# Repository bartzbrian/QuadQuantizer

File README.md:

# QuadQuantizer
quad pitch quant eurorack

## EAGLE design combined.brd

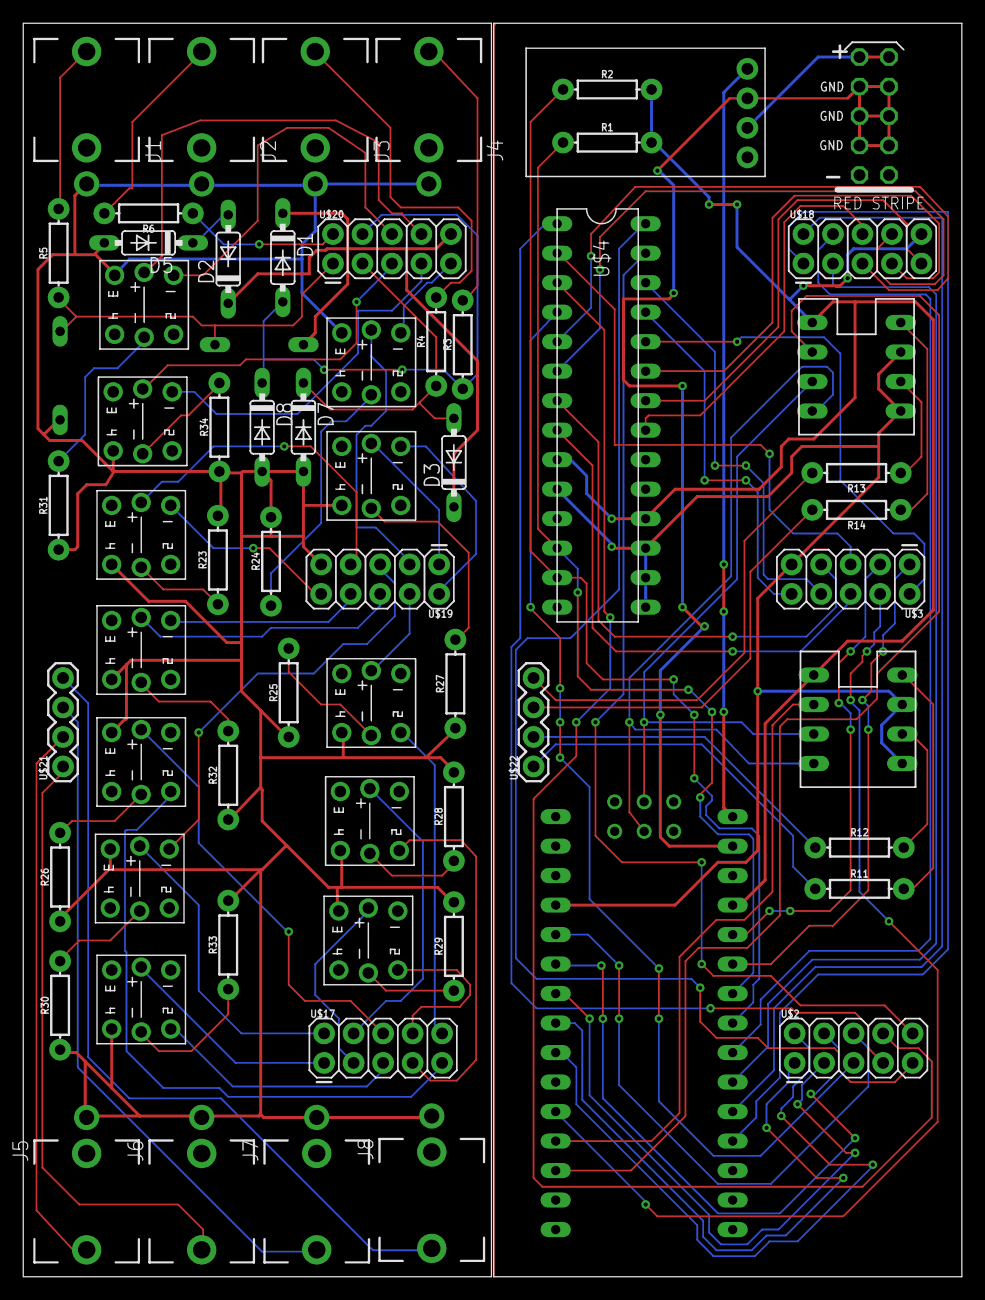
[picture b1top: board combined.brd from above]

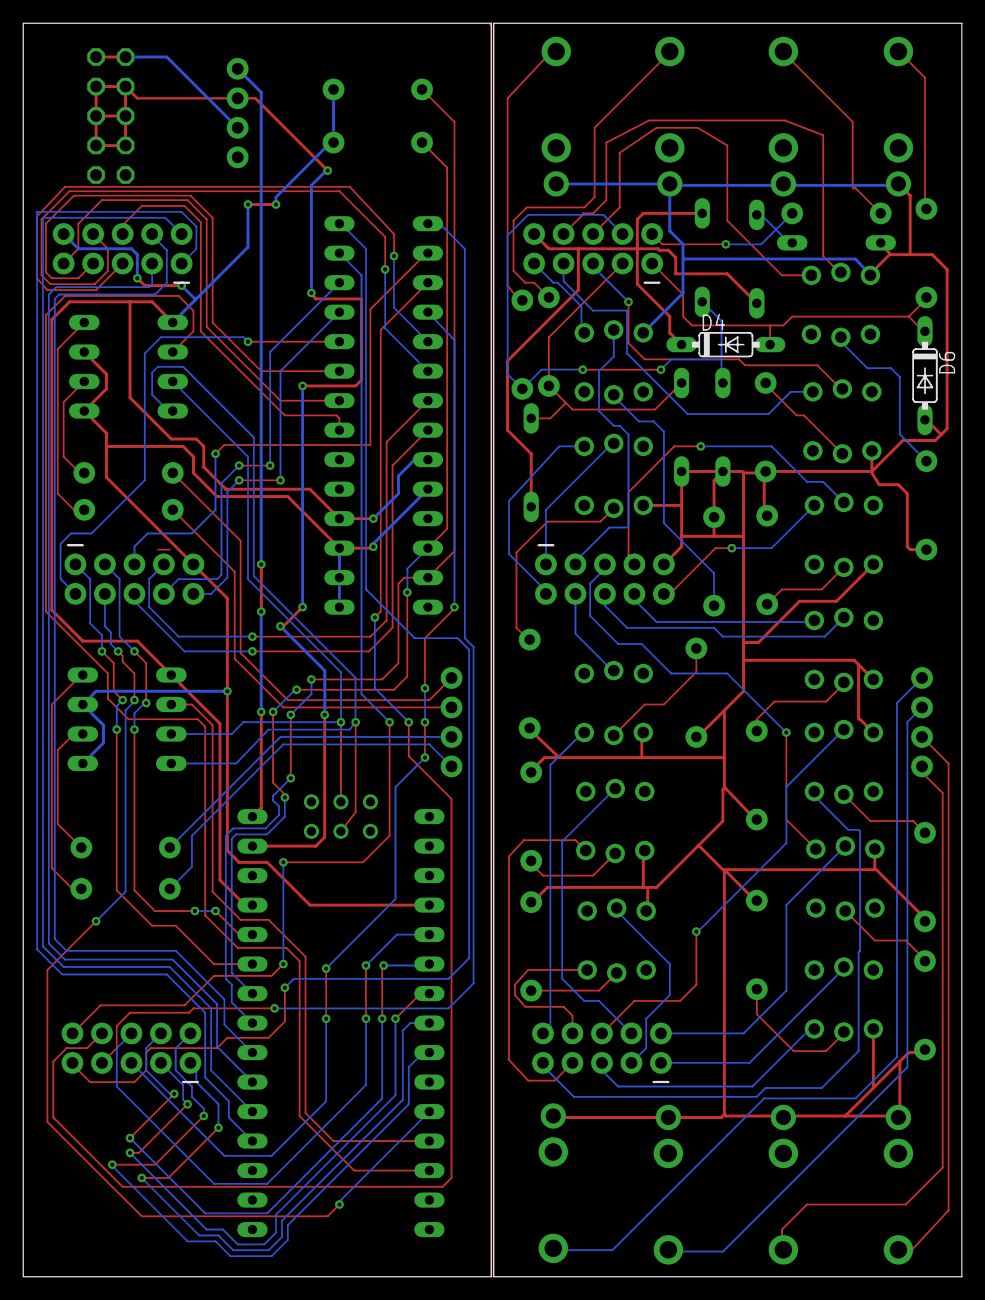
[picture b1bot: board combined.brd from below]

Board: 2 copper layers, 80.8 x 107.9 mm, 64 parts (2 on the bottom side), 84 nets.

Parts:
D1, D2, D3, D4, D5, D6, D7, D8: 1N4148DO35-7; DO35-7
E$1, E$2: 8PIN
J1, J2, J3, J4, J5, J6, J7, J8: THONK35A
POWER: MA05-2
R1, R2, R11, R12, R13, R14: 100; AXIAL-0.3
R3, R4, R5, R6: 10; AXIAL-0.3
R23, R24, R25, R26, R27, R28, R29, R30, R31, R32, R33, R34: 1k; AXIAL-0.3
U$1: NANO
U$2, U$3, U$17, U$18, U$19, U$20: 2X5PEG; 2X5
U$4: DIP28
U$5, U$6, U$7, U$8, U$9, U$10, U$11, U$12, U$13, U$14, U$15, U$16: PB6149L
U$21, U$22: 1X4PEG; 1X04
U$23: DROKMINIVREGULATOR; 1X04

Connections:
unnamed: R13.P$2, U$22.4
unnamed: E$2.12, R12.P$2
unnamed: R14.P$2, U$22.3
unnamed: D4.A, D6.C, R5.P$1, U$20.1
unnamed: D1.C, D2.C, D3.C, D4.C, U$20.10
S$1: U$14.P$2, U$17.1
S$2: U$6.P$2, U$17.2
S$6: D2.A, D5.C, R6.P$1, U$20.2
S$8: D1.A, D8.C, R3.P$1, U$20.4
S$9: E$1.12, R13.P$1
S$10: E$1.14, R14.P$1
S$13: POWER.3, POWER.4, POWER.5, POWER.6, POWER.7, POWER.8, U$23.3
S$14: E$2.2, U$1.D9
S$15: E$1.2, U$1.D10
S$16: D3.A, R4.P$1, U$20.3
S$17: U$7.P$6, U$17.8
S$18: R12.P$1, U$22.2
S$19: R11.P$1, U$22.1
S$20: R34.P$2, U$11.P$5
S$21: R32.P$2, U$5.P$5
S$22: R23.P$1, U$12.P$5
S$23: R31.P$2, U$15.P$5
S$25: R24.P$1, U$10.P$5
S$26: E$1.3, E$2.3, U$1.ICSP3
S$27: E$1.4, E$2.4, U$1.ICSP4
S$28: R28.P$1, U$16.P$5
S$29: R29.P$1, U$7.P$5
S$30: U$1.A0, U$18.1
S$31: U$1.A1, U$18.2
S$32: U$10.P$3, U$15.P$3
S$33: R25.P$2, U$8.P$5
S$34: R26.P$2, U$13.P$5
S$35: R30.P$2, U$6.P$5
S$36: R33.P$1, U$14.P$5
S$38: U$1.A2, U$18.3
S$39: D6.A, R23.P$2, R24.P$2, R26.P$1, R31.P$1, R33.P$2, R34.P$1, U$5.P$4, U$6.P$3, U$9.P$4, U$11.P$4, U$12.P$4, U$13.P$3, U$14.P$4, U$19.9
S$43: U$7.P$2, U$17.3
S$44: U$16.P$2, U$17.4
S$45: U$8.P$2, U$19.4
S$46: U$13.P$2, U$17.6
S$47: U$5.P$2, U$19.6
S$48: U$9.P$2, U$19.1
S$49: U$10.P$2, U$19.3
S$50: U$14.P$6, U$17.5
S$51: U$16.P$6, U$17.7
S$52: U$13.P$6, U$17.9
S$53: U$8.P$6, U$17.10
S$54: U$5.P$1, U$19.8
S$55: U$12.P$2, U$19.7
S$56: U$12.P$1, U$19.10
S$57: U$6.P$1, U$19.5
S$59: POWER.9, POWER.10, U$23.2
S$60: U$1.RAW, U$23.4
S$61: U$11.P$1, U$20.7
S$62: U$9.P$1, U$19.2
S$64: U$15.P$2, U$20.8
S$65: U$11.P$2, U$20.5
S$66: U$4.P$22, U$18.6
S$67: U$4.P$21, U$18.9
S$68: U$4.P$20, U$18.7
S$69: U$3.2, U$4.P$19
S$70: U$3.10, U$4.P$18
S$71: U$3.8, U$4.P$17
S$72: U$2.10, U$4.P$16
S$73: E$1.11, E$1.13, E$2.11, E$2.13, U$1.GND1, U$3.9, U$4.P$10, U$4.P$26, U$4.P$27, U$4.P$28
S$74: U$2.7, U$4.P$1
S$75: U$3.5, U$4.P$2
S$76: U$2.8, U$4.P$3
S$77: U$2.5, U$4.P$4
S$78: U$4.P$5, U$18.5
S$79: U$4.P$6, U$18.8
S$80: U$3.7, U$4.P$7
S$81: U$3.6, U$4.P$8
S$82: R1.P$1, U$1.A5, U$4.P$12
S$83: R2.P$1, U$1.A4, U$4.P$13
S$84: U$1.A6, U$3.1
S$85: U$1.A7, U$3.3
S$86: U$1.D8, U$3.4
S$88: U$1.D2, U$2.6
S$89: U$1.D3, U$2.4
S$90: U$1.D4, U$2.3
S$91: U$1.D5, U$2.1
S$92: U$1.D6, U$2.2
S$94: E$1.1, E$2.1, R1.P$2, R2.P$2, U$1.5V, U$4.P$9, U$4.P$25, U$18.10

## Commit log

2018-04-11 initial commit
    untested, speculative code
2018-07-02 working
    tested, largely functional version, some final tweaks left to make
2018-07-06 Working
    fixed output config, remapped wonky button. basically done
2018-07-07 implemented 7edo easter egg
    added in an easter egg where if the C button is held down when the module is powered on, the scale bank loaded is the 7Edo microtonal scale, which is a scale with 7 equal temperment tones per octave.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
2018-07-07 added board and schematic

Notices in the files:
parts and their libraries:
SparkFun-Resistors: Licensing: Creative Commons ShareAlike 4.0 International - https://creativecommons.org/licenses/by-sa/4.0
